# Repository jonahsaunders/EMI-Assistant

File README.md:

# EMI Assistant for KiCad

**Open a PCB. Click Analyze EMI. See what to investigate next.**

EMI Assistant brings layout screening, circuit comparisons with **ngspice**, and
local trace simulations with **openEMS** into one workflow launched from KiCad.
It opens a native companion window with prioritized findings, explanations,
board navigation, and comparison graphs.

**[Download EMI Assistant 0.2.1](downloads/EMI-Assistant-0.2.1.zip?raw=true)** ·
[User guide](docs/USER-GUIDE.md) · [Simulation details](docs/SIMULATION.md)

Original application code: **MIT**. Copied KiCad schemas and runtime libraries
retain their licenses; see [third-party notices](THIRD_PARTY_NOTICES.md).

## Install and run

1. Download the ZIP above. In **KiCad 10 → Plugin and Content Manager**, choose
   **Install from File** and select it. Apply the installation.
2. In **Preferences → Plugins**, enable **KiCad API** and check that a Python
   interpreter is detected.
3. Restart the PCB Editor, open your board, and click **Analyze EMI**.

The first click may open a preparation window to install the application's
Python dependencies. On **Windows x64**, missing supported solvers are downloaded
automatically from verified official releases. Layout findings appear first;
simulations run in the background. Later runs reuse installed engines and
unchanged results.

No account or PCB upload is required. Analysis runs locally and works offline
after setup. Linux and macOS require installed solver executables; automatic
portable solver downloads currently support Windows x64.

If the button is missing, check **Preferences → PCB Editor → Plugins → Show
Button**. See [installation troubleshooting](docs/INSTALLER-FIX.md).

## What it helps you do

| Task | What you get |
|---|---|
| Find layout risks | Checks for reference-plane gaps, return connections at layer changes, decoupling paths, marked buck/boost layouts, and sensitive or cable-net proximity |
| Understand a finding | Location, evidence, confidence, plain-language guidance, and **Show in KiCad** navigation |
| Compare circuit changes | ngspice capacitor-network impedance, supported RC/LC filter response, and LC ringing before and after a candidate change |
| Investigate a trace | openEMS reflection and voltage-transfer comparisons for a supported local microstrip section with two termination choices |
| Diagnose a measured peak | Clock-harmonic hypotheses, CSV spectrum import, measurement notes, and suggested experiments |
| Share a review | HTML or JSON reports containing findings, numerical comparisons, assumptions, and coverage |

Both enabled solvers start with **Analyze EMI**. You can cancel simulation while
continuing to review layout findings. Optional board context and simulation
settings are remembered with the board.

Want to explore first? Use **Try the example board** for layout findings, or open
[examples/clean.kicad_pcb](examples/clean.kicad_pcb) for a fixture that supports
both solvers. The [example report](docs/example-simulation-report.html) contains
an actual completed solver run.

## Scope and current status

**This is an early release for engineering investigation.** Layout checks are
screening rules. ngspice runs bounded passive models; openEMS runs a local
straight-trace coupon derived from PCB geometry and stackup. Neither is a
whole-board emissions prediction or a compliance result. Unsupported geometry
and missing inputs are reported explicitly.

Saved schematics and custom-symbol pins can enrich the analysis. This release
does not execute arbitrary custom-IC or vendor SPICE models. See
[supported models and assumptions](docs/SIMULATION.md).

The 0.2.0 release passed **286 tests and 32 subtests**, with real Linux ngspice
and openEMS runs documented separately. Native Windows/KiCad GUI execution and
hardware EMC validation remain pending. See the full [validation record and
acceptance checklist](docs/VALIDATION.md).

## Develop or contribute

See [CONTRIBUTING.md](CONTRIBUTING.md) for setup, tests, and package building.
Bug reports with the KiCad version, operating system, and a small reproducible
example are especially useful. Check your board and logs before sharing them.

[Changelog](CHANGELOG.md) · [Application MIT license](LICENSE) · [Third-party licenses](THIRD_PARTY_NOTICES.md)

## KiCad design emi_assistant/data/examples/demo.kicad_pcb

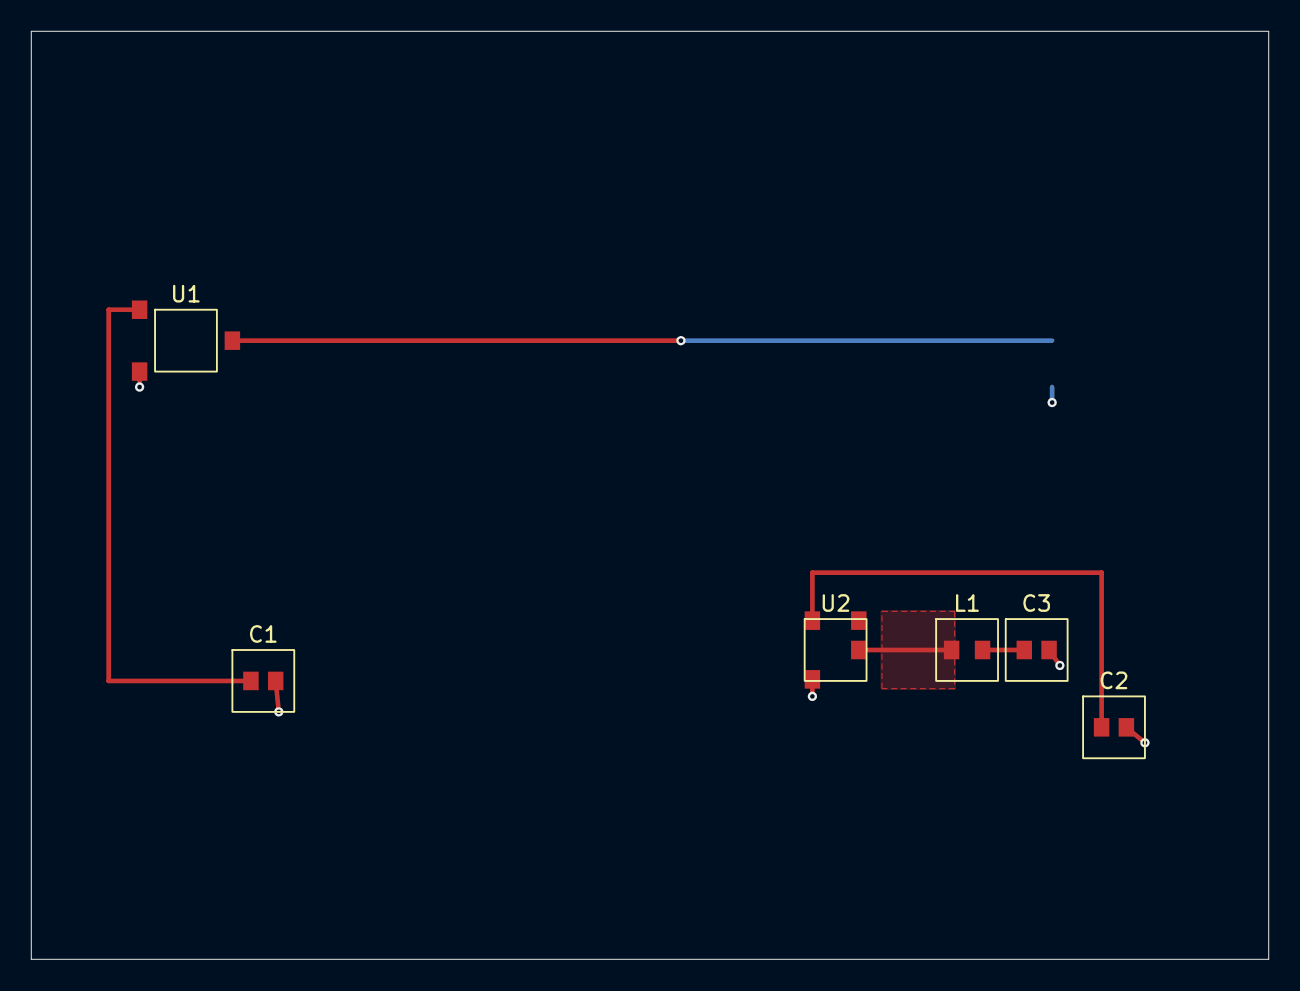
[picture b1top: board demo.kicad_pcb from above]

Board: 4 copper layers, 80.0 x 60.0 mm, 7 parts (1 on the bottom side), 6 nets.

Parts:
C1: 100nF; Capacitor
C2: 10uF; Capacitor
C3: 22uF; Capacitor
J1: External clock; Connector
L1: 10uH; Inductor
U1: 24 MHz controller; Controller
U2: Buck regulator; Buck

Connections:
+3V3: C1.1, U1.1
+5V: C3.1, L1.2
CLK24: J1.1, U1.3
GND: C1.2, C2.2, C3.2, J1.2, U1.2, U2.1
SW: L1.1, U2.2
VIN: C2.1, U2.3
